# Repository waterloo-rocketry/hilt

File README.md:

# HILT

Modular hardware-in-the-loop tester.

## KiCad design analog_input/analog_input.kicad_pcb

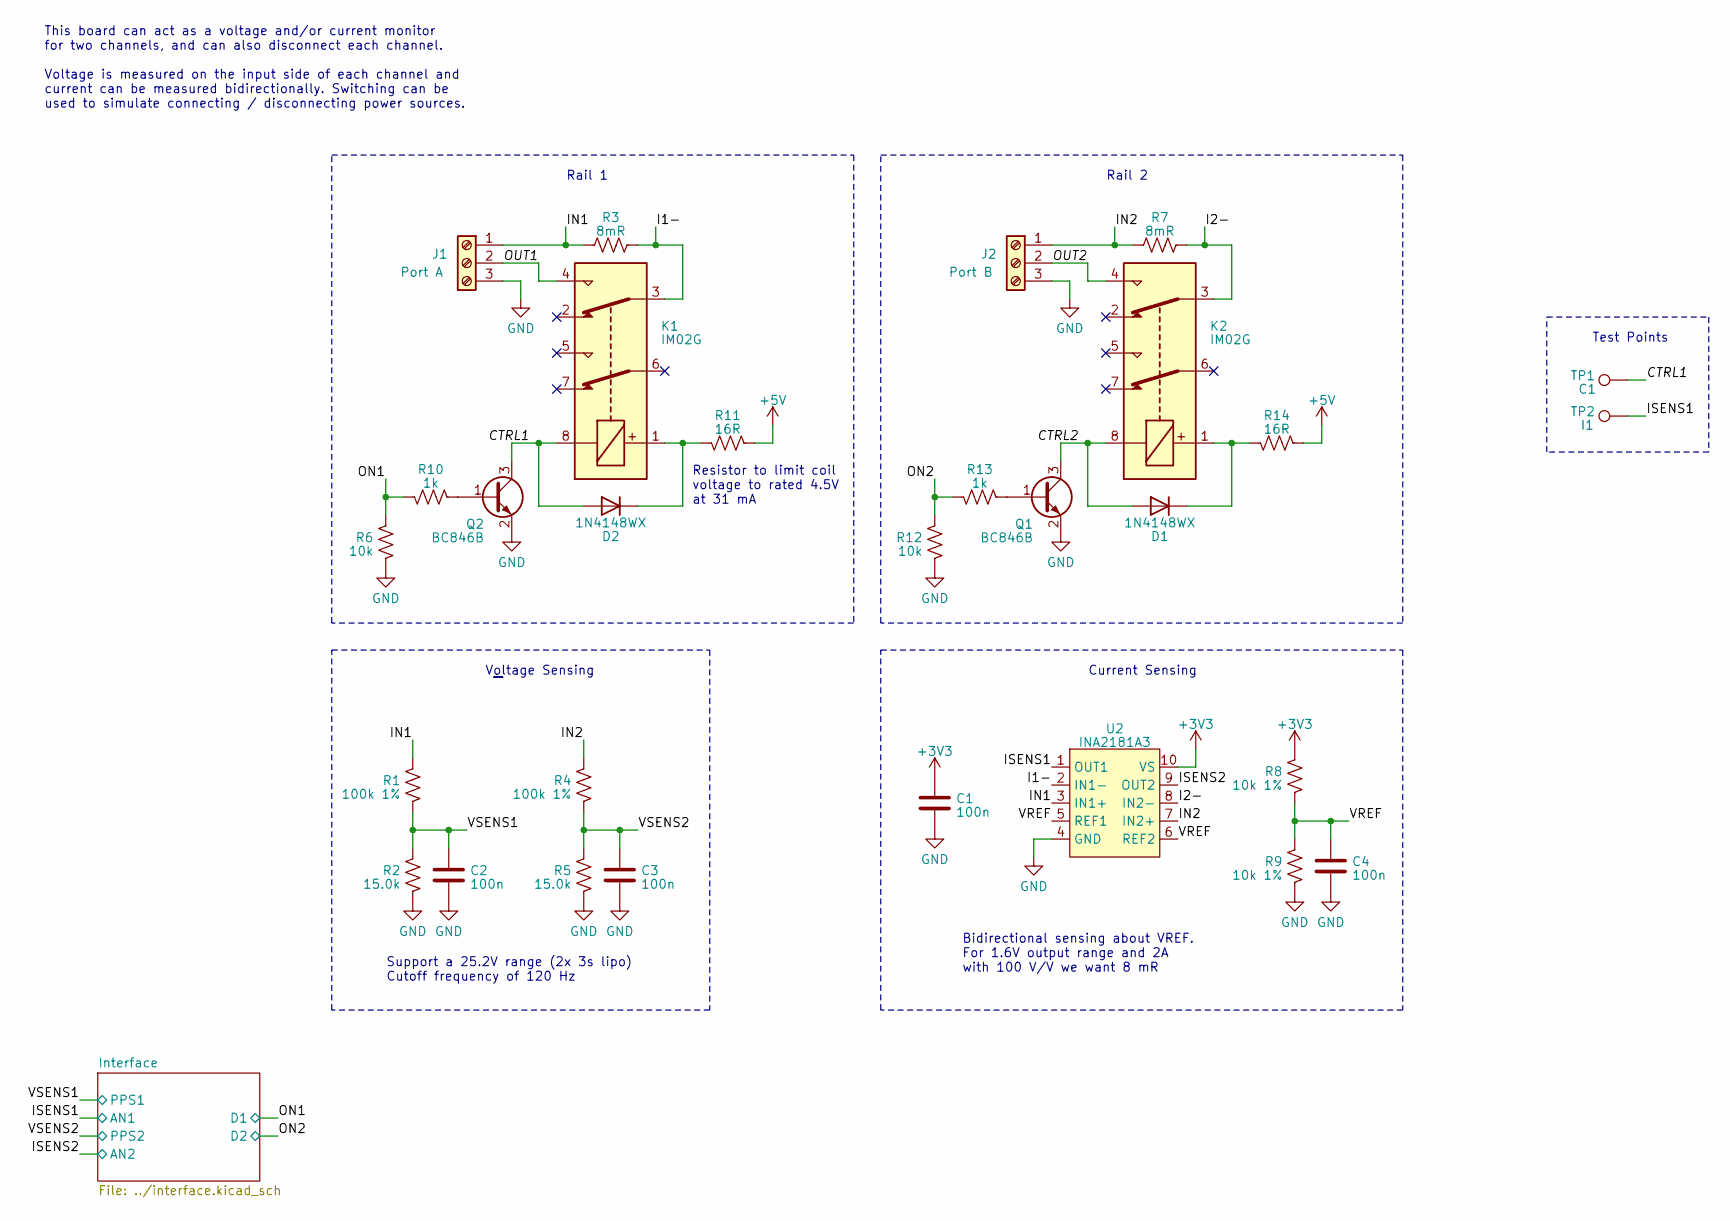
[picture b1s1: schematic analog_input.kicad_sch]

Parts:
C1, C2, C3, C4: 100n; C_0805_2012Metric_Pad1.18x1.45mm_HandSolder
D1, D2: 1N4148WX; D_SOD-323_HandSoldering
J1: Port A; TerminalBlock_Phoenix_PT-1,5-3-3.5-H_1x03_P3.50mm_Horizontal
J2: Port B; TerminalBlock_Phoenix_PT-1,5-3-3.5-H_1x03_P3.50mm_Horizontal
K1, K2: IM02G; Relay_2P2T_10x6mm_TE_IMxxG
Q1, Q2: BC846B; SOT-23
R1, R4: 100k 1%; R_0805_2012Metric_Pad1.20x1.40mm_HandSolder
R2, R5: 15.0k; R_0805_2012Metric_Pad1.20x1.40mm_HandSolder
R3, R7: 8mR; R_1206_3216Metric_Pad1.30x1.75mm_HandSolder
R6, R12: 10k; R_0805_2012Metric_Pad1.20x1.40mm_HandSolder
R8, R9: 10k 1%; R_0805_2012Metric_Pad1.20x1.40mm_HandSolder
R10, R13: 1k; R_0805_2012Metric_Pad1.20x1.40mm_HandSolder
R11, R14: 16R; R_0805_2012Metric_Pad1.20x1.40mm_HandSolder
TP1: C1; TestPoint_Pad_D1.5mm
TP2: I1; TestPoint_Pad_D1.5mm
U2: INA2181A3; VSSOP-10_3x3mm_P0.5mm

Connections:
+3V3: C1.1, R8.2, U2.10 (VS); also elsewhere on the board
+5V: R11.1, R14.1; also elsewhere on the board
/CTRL1: D2.2 (A), K1.8, Q2.3 (C), TP1.1
/CTRL2: D1.2 (A), K2.8, Q1.3 (C)
/I1-: K1.3, R3.2, U2.2 (IN1-)
/I2-: K2.3, R7.2, U2.8 (IN2-)
/IN1: J1.1, R1.2, R3.1, U2.3 (IN1+)
/IN2: J2.1, R4.2, R7.1, U2.7 (IN2+)
/ISENS1: TP2.1, U2.1 (OUT1); also elsewhere on the board
/ISENS2: U2.9 (OUT2); also elsewhere on the board
/ON1: R6.2, R10.2; also elsewhere on the board
/ON2: R12.2, R13.2; also elsewhere on the board
/OUT1: J1.2, K1.4
/OUT2: J2.2, K2.4
/VREF: C4.1, R8.1, R9.1, U2.5 (REF1), U2.6 (REF2)
/VSENS1: C2.1, R1.1, R2.1; also elsewhere on the board
/VSENS2: C3.1, R4.1, R5.1; also elsewhere on the board
GND: C1.2, C2.2, C3.2, C4.2, J1.3, J2.3, Q1.2 (E), Q2.2 (E), R2.2, R5.2, R6.1, R9.2, R12.1, U2.4 (GND); also elsewhere on the board
unnamed: D1.1 (K), K2.1, R14.2
unnamed: D2.1 (K), K1.1, R11.2
unnamed: Q1.1 (B), R13.1
unnamed: Q2.1 (B), R10.1

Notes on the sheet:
Current Sensing
Test Points
Support a 25.2V range (2x 3s lipo) Cutoff frequency of 120 Hz
This board can act as a voltage and/or current monitor for two channels, and can also disconnect each channel. Voltage is measured on the input side of each channel and current can be measured bidirectionally. Switching can be used to simulate connecting / disconnecting power sources.
Rail 2
Resistor to limit coil voltage to rated 4.5V at 31 mA
Bidirectional sensing about VREF. For 1.6V output range and 2A with 100 V/V we want 8 mR
Voltage Sensing
Rail 1

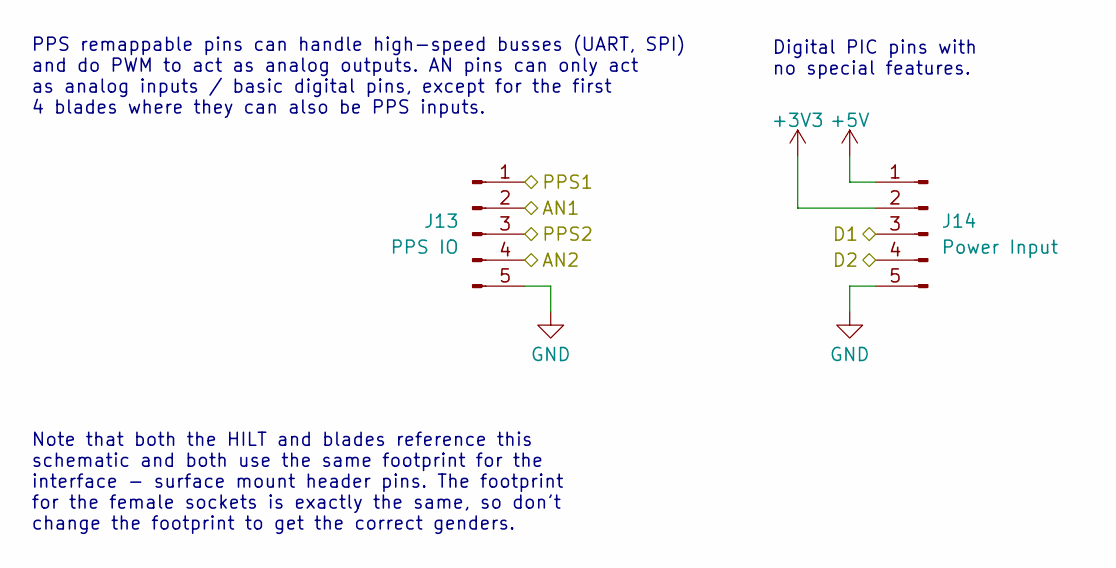
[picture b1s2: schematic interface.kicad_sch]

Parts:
J13: PPS IO; PinHeader_1x05_P2.54mm_Vertical_SMD_Pin1Left
J14: Power Input; PinHeader_1x05_P2.54mm_Vertical_SMD_Pin1Left

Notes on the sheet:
Digital PIC pins with no special features.
PPS remappable pins can handle high-speed busses (UART, SPI) and do PWM to act as analog outputs. AN pins can only act as analog inputs / basic digital pins, except for the first 4 blades where they can also be PPS inputs.
Note that both the HILT and blades reference this schematic and both use the same footprint for the interface - surface mount header pins. The footprint for the female sockets is exactly the same, so don't change the footprint to get the correct genders.

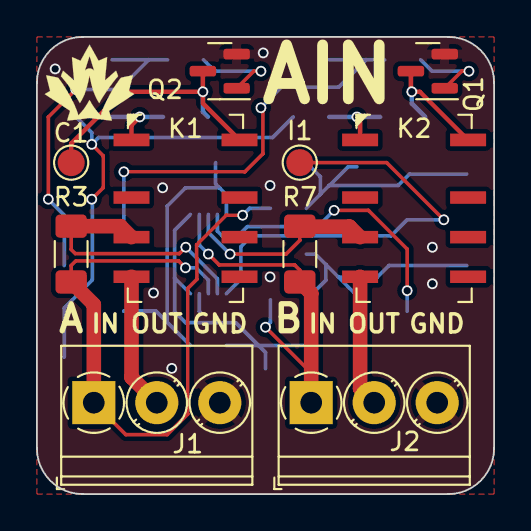
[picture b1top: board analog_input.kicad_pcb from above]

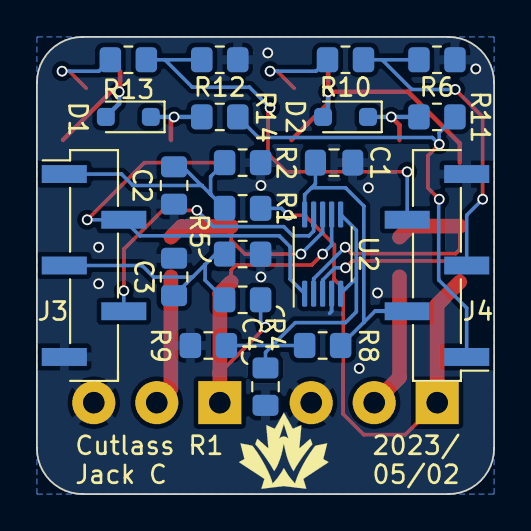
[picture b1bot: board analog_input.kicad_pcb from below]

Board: 2 copper layers, 25.4 x 25.4 mm, 31 parts (21 on the bottom side), 22 nets.

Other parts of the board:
J3: PPS IO; PinHeader_1x05_P2.54mm_Vertical_SMD_Pin1Left
J4: Power Input; PinHeader_1x05_P2.54mm_Vertical_SMD_Pin1Left

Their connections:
+3V3: J4.2; also elsewhere on the board
+5V: J4.1; also elsewhere on the board
/ISENS1: J3.2; also elsewhere on the board
/ISENS2: J3.4; also elsewhere on the board
/ON1: J4.3; also elsewhere on the board
/ON2: J4.4; also elsewhere on the board
/VSENS1: J3.1; also elsewhere on the board
/VSENS2: J3.3; also elsewhere on the board
GND: J3.5, J4.5; also elsewhere on the board

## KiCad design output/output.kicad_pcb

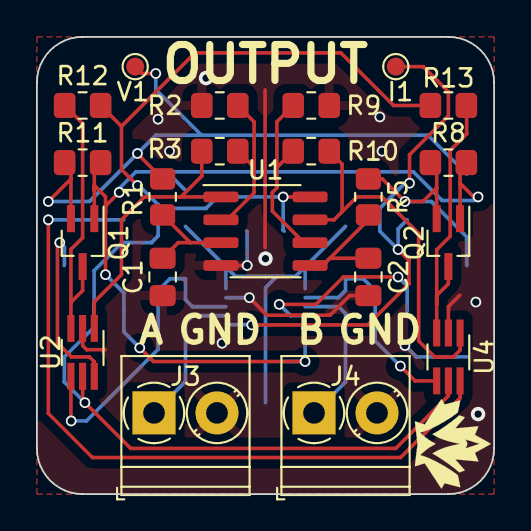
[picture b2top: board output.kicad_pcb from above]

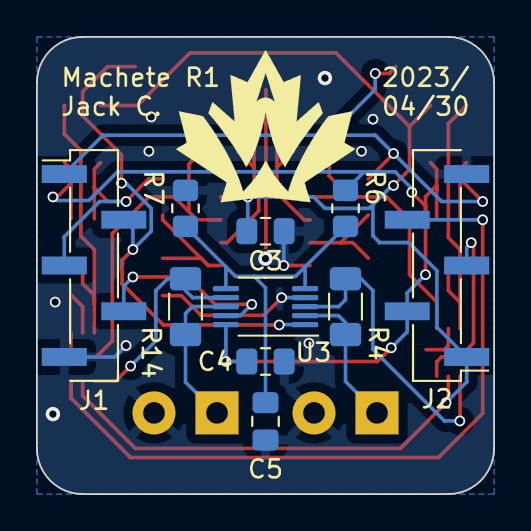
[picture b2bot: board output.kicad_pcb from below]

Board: 2 copper layers, 25.4 x 25.4 mm, 31 parts (10 on the bottom side), 22 nets.

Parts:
C1, C2: 330n; C_0805_2012Metric_Pad1.18x1.45mm_HandSolder
C3, C4, C5: 100n; C_0805_2012Metric_Pad1.18x1.45mm_HandSolder
J1: PPS IO; PinHeader_1x05_P2.54mm_Vertical_SMD_Pin1Left
J2: Power Input; PinHeader_1x05_P2.54mm_Vertical_SMD_Pin1Left
J3: Output A; TerminalBlock_Phoenix_PT-1,5-2-3.5-H_1x02_P3.50mm_Horizontal
J4: Output B; TerminalBlock_Phoenix_PT-1,5-2-3.5-H_1x02_P3.50mm_Horizontal
Q1, Q2: BSS138; SOT-323_SC-70_Handsoldering
R1, R5: 5k; R_0805_2012Metric_Pad1.20x1.40mm_HandSolder
R2, R9: 32.4k; R_0805_2012Metric_Pad1.20x1.40mm_HandSolder
R3, R10: 16.9k; R_0805_2012Metric_Pad1.20x1.40mm_HandSolder
R4, R14: 150mR; R_1206_3216Metric_Pad1.30x1.75mm_HandSolder
R6, R7: 10k 1%; R_0805_2012Metric_Pad1.20x1.40mm_HandSolder
R8, R11: 10k; R_0805_2012Metric_Pad1.20x1.40mm_HandSolder
R12, R13: 1k; R_0805_2012Metric_Pad1.20x1.40mm_HandSolder
TP1: V1; TestPoint_Pad_D1.0mm
TP2: I1; TestPoint_Pad_D1.0mm
U1: OPA2990; SOIC-8_3.9x4.9mm_P1.27mm
U2, U4: SN74LVC1G3157; SOT-363_SC-70-6_Handsoldering
U3: INA2181; VSSOP-10_3x3mm_P0.5mm

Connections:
+3V3: C4.1, J2.2, Q1.1 (G), Q2.1 (G), R6.2, R8.2, R11.2, U3.10 (VS)
+5V: C3.1, J2.1, R12.2, R13.2, U1.8 (V+), U2.5 (VCC), U4.5 (VCC)
/A~D1: J2.3, U2.6 (S)
/A~D2: J2.4, U4.6 (S)
/I1: J1.2, TP2.1, U3.1 (OUT1)
/I1+: R4.1, U2.4 (A), U3.3 (IN1+)
/I2: J1.4, U3.9 (OUT2)
/I2+: R14.1, U3.7 (IN2+), U4.4 (A)
/OUT1: J3.1, R4.2, U3.2 (IN1-)
/OUT1A: R3.2, U1.1, U2.1 (B2)
/OUT1D: Q1.3 (D), R12.1, U2.3 (B1)
/OUT2: J4.1, R14.2, U3.8 (IN2-)
/OUT2A: R10.2, U1.7, U4.1 (B2)
/OUT2D: Q2.3 (D), R13.1, U4.3 (B1)
/REF: C5.1, R6.1, R7.1, U3.5 (REF1), U3.6 (REF2)
/V1: J1.1, Q1.2 (S), R1.1, R11.1, TP1.1
/V2: J1.3, Q2.2 (S), R5.1, R8.1
GND: C1.2, C2.2, C3.2, C4.2, C5.2, J1.5, J2.5, J3.2, J4.2, R2.1, R7.2, R9.1, U1.4 (V-), U2.2 (GND), U3.4 (GND), U4.2 (GND)
unnamed: C1.1, R1.2, U1.3 (+)
unnamed: R2.2, R3.1, U1.2 (-)
unnamed: C2.1, R5.2, U1.5 (+)
unnamed: R9.2, R10.1, U1.6 (-)

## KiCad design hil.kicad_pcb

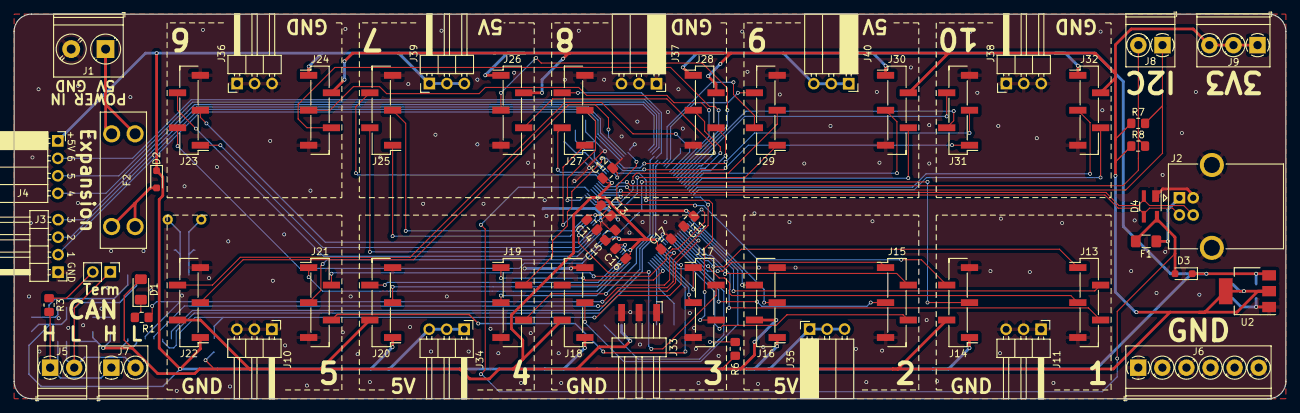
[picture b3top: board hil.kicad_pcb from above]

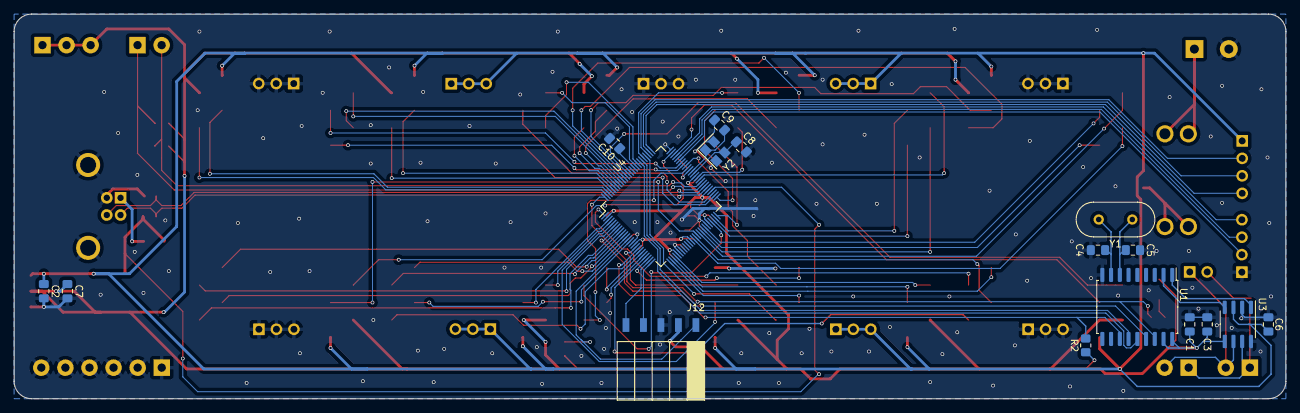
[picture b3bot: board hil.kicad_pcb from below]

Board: 2 copper layers, 184.8 x 55.9 mm, 76 parts (17 on the bottom side), 96 nets.

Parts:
C1, C3, C6, C11, C12, C13, C14, C15, C16, C17: 100n; C_0805_2012Metric_Pad1.18x1.45mm_HandSolder
C2, C10: 10u; C_0805_2012Metric_Pad1.18x1.45mm_HandSolder
C4, C5: 27p; C_0805_2012Metric_Pad1.18x1.45mm_HandSolder
C7: 22u; C_0805_2012Metric_Pad1.18x1.45mm_HandSolder
C8, C9: DNP; C_0805_2012Metric_Pad1.18x1.45mm_HandSolder
D1: RED 2V; LED_1206_3216Metric_Pad1.42x1.75mm_HandSolder
D2, D3: CUS10S30; D_SOD-323_HandSoldering
D4: ESDALD05UJ2X; SOT-143_Handsoldering
F1: 500 mA; Fuse_1206_3216Metric_Pad1.42x1.75mm_HandSolder
F2: 1A; Fuseholder_36-3557-15-ND
J1: 5V In; TerminalBlock_Phoenix_PT-1,5-2-5.0-H_1x02_P5.00mm_Horizontal
J2: USB_B; USB_B_OST_USB-B1HSxx_Horizontal
J3: IO A; PinHeader_1x04_P2.54mm_Horizontal
J4: IO B; PinSocket_1x04_P2.54mm_Horizontal
J5: CAN B; TerminalBlock_Phoenix_PT-1,5-2-3.5-H_1x02_P3.50mm_Horizontal
J6: GND; TerminalBlock_Phoenix_PT-1,5-6-3.5-H_1x06_P3.50mm_Horizontal
J7: CAN A; TerminalBlock_Phoenix_PT-1,5-2-3.5-H_1x02_P3.50mm_Horizontal
J8: I2C; TerminalBlock_Phoenix_PT-1,5-2-3.5-H_1x02_P3.50mm_Horizontal
J9: 3V3; TerminalBlock_Phoenix_PT-1,5-3-3.5-H_1x03_P3.50mm_Horizontal
J10: GND1; PinHeader_1x03_P2.54mm_Horizontal
J11: GND3; PinHeader_1x03_P2.54mm_Horizontal
J12: Programming Connector; PinHeader_5x2.54_SMD_90deg_952-3198-1-ND
J13, J15, J17, J19, J21, J23, J25, J27, J29, J31: PPS IO; PinHeader_1x05_P2.54mm_Vertical_SMD_Pin1Left
J14, J16, J18, J20, J22, J24, J26, J28, J30, J32: Power Input; PinHeader_1x05_P2.54mm_Vertical_SMD_Pin1Left
J33: GND2; Harwin_M20-89003xx_1x03_P2.54mm_Horizontal
J34: 5V1; PinHeader_1x03_P2.54mm_Horizontal
J35: 5V2; PinSocket_1x03_P2.54mm_Horizontal
J36: GND4; PinHeader_1x03_P2.54mm_Horizontal
J37: GND5; PinSocket_1x03_P2.54mm_Horizontal
J38: GND6; PinHeader_1x03_P2.54mm_Horizontal
J39: 5V3; PinHeader_1x03_P2.54mm_Horizontal
J40: 5V4; PinSocket_1x03_P2.54mm_Horizontal
JP1: Term; PinHeader_1x02_P2.54mm_Vertical
R1: 270R; R_0805_2012Metric_Pad1.20x1.40mm_HandSolder
R2, R6: 10k; R_0805_2012Metric_Pad1.20x1.40mm_HandSolder
R3: 120R; R_0805_2012Metric_Pad1.20x1.40mm_HandSolder
R7, R8: 4.7k; R_0805_2012Metric_Pad1.20x1.40mm_HandSolder
U1: MCP2515; SOIC-18W_7.5x11.6mm_P1.27mm
U2: AZ1117-3.3; SOT-223-3_TabPin2
U3: MCP2562; SOIC-8_3.9x4.9mm_P1.27mm
U4: PIC24FJ128GC010; TQFP-100_12x12mm_P0.4mm
Y1: 12 MHz; Crystal_HC49-4H_Vertical
Y2: 48 MHz DNP; Crystal_SMD_Abracon_ABM8G-4Pin_3.2x2.5mm

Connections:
+3V3: C1.1, C3.1, C7.1, C11.1, C12.1, C13.1, C14.1, C15.1, C16.1, C17.1, D1.2 (A), J9.1, J9.2, J9.3, J12.2, J14.2, J16.2, J18.2, J20.2, J22.2, J24.2, J26.2, J28.2, J30.2, J32.2, R2.1, R6.1, R7.1, R8.1, U1.17 (~RESET), U1.18 (VDD), U2.2 (VO), U3.5 (VIO), U4.2 (VDD), U4.16 (VDD), U4.30 (AVDD), U4.37 (SVDD), U4.46 (VDD), U4.55 (VUSB3V3), U4.62 (VDD)
+5V: C2.1, C6.1, D2.1 (K), D3.1 (K), J4.1, J14.1, J16.1, J18.1, J20.1, J22.1, J24.1, J26.1, J28.1, J30.1, J32.1, J34.1, J34.2, J34.3, J35.1, J35.2, J35.3, J39.1, J39.2, J39.3, J40.1, J40.2, J40.3, U2.3 (VI), U3.3 (VDD)
/AI1: J13.2, U4.6 (AN8/OA1N1/RPI38/RC1)
/AI2: J13.4, U4.8 (AN9/RPI40/RC3)
/AI3: J15.2, U4.9 (AN16/RPI41/RC4)
/AI4: J15.4, U4.19 (AN21/RPI34/RE9)
/AI5: J17.2, U4.47 (AN28/RPI43/RD14)
/AI6: J17.4, U4.66 (AN38/RPI36/SCL1/OCTRIG2/RA14)
/AI7: J19.2, U4.67 (AN39/RPI35/SDA1/RA15)
/AI8: J19.4, U4.79 (AN45/RPI42/RD12)
/AI9: J21.2, U4.1 (AN33/CTED3/RG15)
/AI10: J21.4, U4.22 (AN3/OA2OUT/C2INA/VPIO/RB3)
/AI11: J23.2, U4.38 (TCK/AN26/RA1)
/AI12: J23.4, U4.41 (AN12/COM5/T1CK/CTED2/RB12)
/AI13: J25.2, U4.42 (AN13/OA2P3/DAC2/CTED1/RB13)
/AI14: J25.4, U4.60 (TDI/AN36/RA4)
/AI15: J27.2, U4.61 (TDO/AN37/RA5)
/AI16: J27.4, U4.80 (AN46/RD13)
/AI17: J29.2, U4.83 (AN34/OA1P2/C3INB/RD6)
/AI18: J29.4, U4.84 (AN20/C3INA/RD7)
/AI19: J31.2, U4.91 (AN23/RA6)
/AI20: J31.4, U4.92 (AN22/RA7)
/AO1: J13.1, U4.10 (BGBUF2/AN17/OA1P1/C1IND/RP21/T5CK/RG6)
/AO2: J13.3, U4.11 (VLCAP1/AN18/OA1N4/C1INC/RP26/RG7)
/AO3: J15.1, U4.12 (VLCAP2/AN19/OA1N2/C2IND/RP19/RG8)
/AO4: J15.3, U4.14 (AN49/OA1P0/C2INC/DAC1/RP27/RG9)
/AO5: J17.1, U4.20 (PGEC3/AN5/OA1OUT/C1INA/RP18/RB5)
/AO6: J17.3, U4.21 (PGED3/AN4/OA1N0/C1INB/RP28/USBOEN/RB4)
/AO7: J19.1, U4.23 (AN2/OA2N2/CTCMP/C2INB/RP13/T4CK/VMIO/CT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)
/AO8: J19.3, U4.26 (PGEC2/AN6/OA1P3/RP6/LCDBIAS3/RB6)
/AO9: J21.1, U4.27 (PGED2/AN7/COM6/RP7/RB7)
/AO10: J21.3, U4.39 (AN27/RP31/RF13)
/AO11: J23.1, U4.43 (AN14/OA2N4/RP14/CTED5/CTPLS/RB14)
/AO12: J23.3, U4.44 (AN15/RP29/T2CK/REFO/CTED6/RB15)
/AO13: J25.1, U4.48 (AN29/RP5/RD15)
/AO14: J25.3, U4.49 (AN11/OA2N3/RP10/SDA2/T3CK/RF4)
/AO15: J27.1, U4.50 (CVREF/AN10/OA2P2/RP17/SCL2/RF5)
/AO16: J27.3, U4.51 (AN30/RP16/USBID/RF3)
/AO17: J29.1, U4.52 (AN31/RP30/RF2)
/AO18: J29.3, U4.53 (AN32/RP15/RF8)
/AO19: J31.1, U4.68 (AN40/RP2/RTCC/DMLN/OCTRIG1/RD8)
/AO20: J31.3, U4.69 (AN24/RP4/DPLN/RD9)
/CANH: J5.1, J7.1, R3.2, U3.7 (CANH)
/CANL: J5.2, J7.2, JP1.1 (A), U3.6 (CANL)
/D5: J14.3, U4.40 (RPI32/CTED7/RF12)
/D6: J14.4, U4.74 (PWRLCLK/SOSCO/SCLKI/RPI37/RC14)
/D7: J16.3, U4.3 (CTED4/LCDBIAS2/RE5)
/D8: J16.4, U4.4 (LCDBIAS1/RE6)
/D9: J18.3, U4.5 (LCDBIAS0/RE7)
/D10: J18.4, U4.17 (TMS/CTED0/RA0)
/D11: J20.3, U4.28 (CVREF-/AVREF-/RA9)
/D12: J20.4, U4.29 (CVREF+/AVREF+/RA10)
/D13: J22.3, U4.73 (SOSCI/RC13)
/D14: J22.4, U4.87 (COM7/VCMPST1/RF0)
/D15: J24.3, U4.88 (COM4/VCMPST2/RF1)
/D16: J24.4, U4.89 (RG1)
/D17: J26.3, U4.90 (RG0)
/D18: J26.4, U4.93 (COM3/RE0)
/D19: J28.3, U4.94 (COM2/RE1)
/D20: J28.4, U4.95 (CTED11/RG14)
/D21: J30.3, U4.96 (RG12)
/D22: J30.4, U4.97 (CTED10/RG13)
/D23: J32.3, U4.98 (COM1/RE2)
/D24: J32.4, U4.99 (COM0/CTED9/RE3)
/D+: D4.2 (I/O1), J2.3 (D+), U4.57 (D+/RG2)
/D-: D4.3 (I/O2), J2.2 (D-), U4.56 (D-/RG3)
/IO1: J3.2, U4.70 (AN41/C3IND/RP3/CS2/RD10)
/IO2: J3.3, U4.71 (AN42/OA2P0/C3INC/RP12/CS1/RD11)
/IO3: J3.4, U4.72 (AN43/OA2N0/RP11/VCMPST3/DMH/INT0/RD0)
/IO4: J4.4, U4.76 (AN35/RP24/RD1)
/IO5: J4.3, U4.77 (AN25/OA2N1/RP23/DPH/RD2)
/IO6: J4.2, U4.78 (AN44/OA2P4/RP22/RD3)
/MCU/OSC1: C8.2, U4.63 (OSCI/CLKI/RC12), Y2.3
/MCU/OSC2: C9.2, U4.64 (OSCO/CLKO/RC15), Y2.1
/MCU/PGC: J12.5, U4.24 (PGEC1/CVREF-/AVREF-/AN1/OA2P1/RP1/CTED1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)
/MCU/PGD: J12.4, U4.25 (PGED1/CVREF+/AVREF+/DVREF+/BGBUF1/AN0/R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)
/MCU/~MCLR: J12.1, R6.2, U4.13 (MCLR)
/MISO: U1.15 (SO), U4.7 (RPI39/RC2)
/MOSI: U1.14 (SI), U4.82 (AN48/OA1N1/RP20/RD5)
/OSC1: C4.1, U1.8 (OSC1), Y1.2
/OSC2: C5.1, U1.7 (OSC2), Y1.1
/SCK: U1.13 (SCK), U4.81 (AN47/OA1P4/RP25/RD4)
/SCL: J8.1, R7.2, U4.58 (SCL2/RA2)
/SDA: J8.2, R8.2, U4.59 (SDA2/RA3)
/VUSB: D3.2 (A), D4.4 (VCC), F1.2, U4.54 (VBUS)
/~CS: R1.2, U1.16 (~CS), U4.100 (HLVDIN/CTED8/RE4)
/~INT: R2.2, U1.12 (~INT), U4.18 (RPI33/RE8)
GND: C1.2, C2.2, C3.2, C4.2, C5.2, C6.2, C7.2, C8.1, C9.1, C10.2, C11.2, C12.2, C13.2, C14.2, C15.2, C16.2, C17.2, D4.1 (GND), J1.2, J2.4 (GND), J2.5 (Shield), J3.1, J6.1, J6.2, J6.3, J6.4, J6.5, J6.6, J10.1, J10.2, J10.3, J11.1, J11.2, J11.3, J12.3, J13.5, J14.5, J15.5, J16.5, J17.5, J18.5, J19.5, J20.5, J21.5, J22.5, J23.5, J24.5, J25.5, J26.5, J27.5, J28.5, J29.5, J30.5, J31.5, J32.5, J33.1, J33.2, J33.3, J36.1, J36.2, J36.3, J37.1, J37.2, J37.3, J38.1, J38.2, J38.3, U1.9 (VSS), U2.1 (GND), U3.2 (VSS), U3.8 (STBY), U4.15 (VSS), U4.31 (AVSS), U4.32 (SVSS), U4.45 (VSS), U4.65 (VSS), U4.75 (VSS), Y2.2, Y2.4
unnamed: D1.1 (K), R1.1
unnamed: D2.2 (A), F2.2
unnamed: F2.1, J1.1
unnamed: F1.1, J2.1 (VBUS)
unnamed: JP1.2 (B), R3.1
unnamed: U1.2 (RXCAN), U3.4 (RXD)
unnamed: U1.1 (TXCAN), U3.1 (TXD)
unnamed: C10.1, U4.85 (VCAP)

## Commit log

2023-04-23 Add HILT and analog io modules
2023-05-06 Address review comments, finish routing HILT main board
2023-05-17 Address review comments
